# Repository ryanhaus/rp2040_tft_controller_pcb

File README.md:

# rp2040_tft_controller_pcb
 RP2040-based controller board for the [MI0284QT-11 TFT LCD](https://www.adafruit.com/product/1774) (ILI9341 controller chip) designed in KiCad.<br />
 Future plans are to modify this board to have an FPGA controlling the actual LCD, acting as a GPU, allowing the RP2040 (or another microcontroller) to run more complex programs, see my [ili9341_controller repository](https://github.com/ryanhaus/ili9341_controller).

## PCB Screenshots

## Schematics
Schematics for this PCB can be found in the top directory.<br/>
PDF printouts can be found in the [pdfs](https://github.com/ryanhaus/rp2040_tft_controller_pcb/tree/99923349eaa0201b7b87c9602e28e256294b100d/pdfs) folder.

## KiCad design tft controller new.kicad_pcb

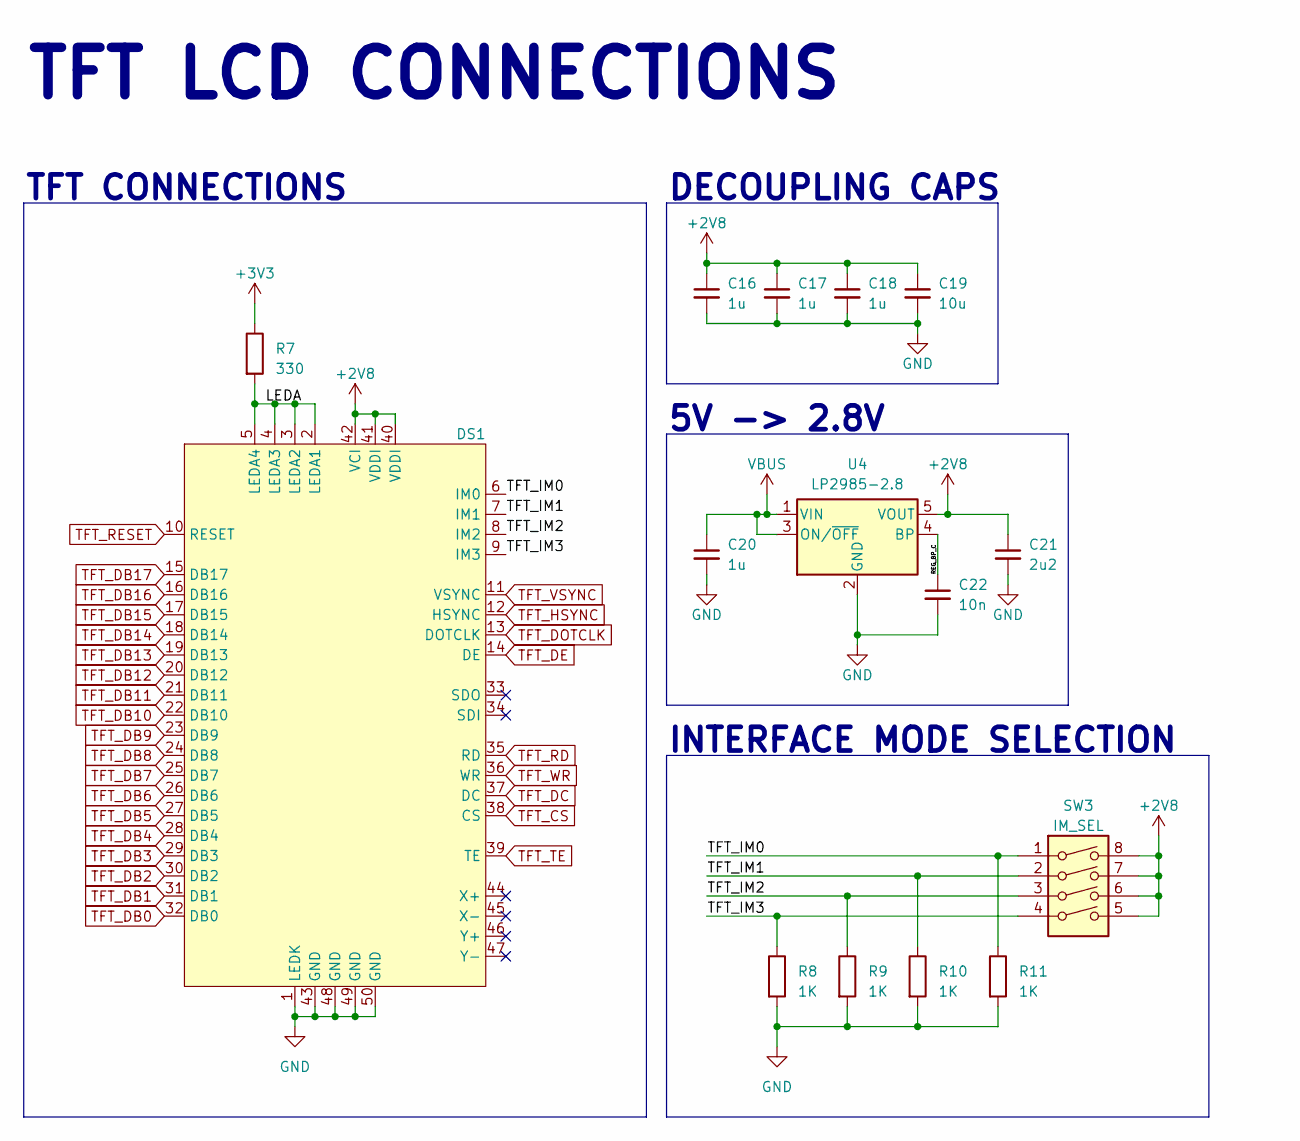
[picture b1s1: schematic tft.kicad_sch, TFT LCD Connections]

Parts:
C16, C17, C18, C20: 1u; C_0603_1608Metric_Pad1.08x0.95mm_HandSolder
C19: 10u; C_0603_1608Metric_Pad1.08x0.95mm_HandSolder
C21: 2u2; C_0603_1608Metric_Pad1.08x0.95mm_HandSolder
C22: 10n; C_0603_1608Metric_Pad1.08x0.95mm_HandSolder
DS1: Molex_54132-5033_1x50-1MP_P0.5mm_Horizontal
R7: 330; R_0603_1608Metric_Pad0.98x0.95mm_HandSolder
R8, R9, R10, R11: 1K; R_0603_1608Metric_Pad0.98x0.95mm_HandSolder
SW3: IM_SEL; SW_DIP_SPSTx04_Slide_9.78x12.34mm_W7.62mm_P2.54mm
U4: LP2985-2.8; SOT-23-5

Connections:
+2V8: C16.1, C17.1, C18.1, C19.1, C21.1, DS1.40 (VDDI), DS1.41 (VDDI), DS1.42 (VCI), SW3.5, SW3.6, SW3.7, SW3.8, U4.5 (VOUT)
+3V3: R7.1; also elsewhere on the board
/TFT LCD Connections/LEDA: DS1.2 (LEDA1), DS1.3 (LEDA2), DS1.4 (LEDA3), DS1.5 (LEDA4), R7.2
/TFT LCD Connections/REG_BP_C: C22.1, U4.4 (BP)
/TFT LCD Connections/TFT_IM0: DS1.6 (IM0), R11.1, SW3.1
/TFT LCD Connections/TFT_IM1: DS1.7 (IM1), R10.1, SW3.2
/TFT LCD Connections/TFT_IM2: DS1.8 (IM2), R9.1, SW3.3
/TFT LCD Connections/TFT_IM3: DS1.9 (IM3), R8.1, SW3.4
GND: C16.2, C17.2, C18.2, C19.2, C20.2, C21.2, C22.2, DS1.1 (LEDK), DS1.43 (GND), DS1.48 (GND), DS1.49 (GND), DS1.50 (GND), R8.2, R9.2, R10.2, R11.2, U4.2 (GND); also elsewhere on the board
TFT_CS: DS1.38 (CS); also elsewhere on the board
TFT_DB0: DS1.32 (DB0); also elsewhere on the board
TFT_DB1: DS1.31 (DB1); also elsewhere on the board
TFT_DB2: DS1.30 (DB2); also elsewhere on the board
TFT_DB3: DS1.29 (DB3); also elsewhere on the board
TFT_DB4: DS1.28 (DB4); also elsewhere on the board
TFT_DB5: DS1.27 (DB5); also elsewhere on the board
TFT_DB6: DS1.26 (DB6); also elsewhere on the board
TFT_DB7: DS1.25 (DB7); also elsewhere on the board
TFT_DB8: DS1.24 (DB8); also elsewhere on the board
TFT_DB9: DS1.23 (DB9); also elsewhere on the board
TFT_DB10: DS1.22 (DB10); also elsewhere on the board
TFT_DB11: DS1.21 (DB11); also elsewhere on the board
TFT_DB12: DS1.20 (DB12); also elsewhere on the board
TFT_DB13: DS1.19 (DB13); also elsewhere on the board
TFT_DB14: DS1.18 (DB14); also elsewhere on the board
TFT_DB15: DS1.17 (DB15); also elsewhere on the board
TFT_DB16: DS1.16 (DB16); also elsewhere on the board
TFT_DB17: DS1.15 (DB17); also elsewhere on the board
TFT_DC: DS1.37 (DC); also elsewhere on the board
TFT_DE: DS1.14 (DE); also elsewhere on the board
TFT_DOTCLK: DS1.13 (DOTCLK); also elsewhere on the board
TFT_HSYNC: DS1.12 (HSYNC); also elsewhere on the board
TFT_RD: DS1.35 (RD); also elsewhere on the board
TFT_RESET: DS1.10 (RESET); also elsewhere on the board
TFT_TE: DS1.39 (TE); also elsewhere on the board
TFT_VSYNC: DS1.11 (VSYNC); also elsewhere on the board
TFT_WR: DS1.36 (WR); also elsewhere on the board
VBUS: C20.1, U4.1 (VIN), U4.3 (ON/~OFF); also elsewhere on the board

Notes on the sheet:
TFT CONNECTIONS
DECOUPLING CAPS
INTERFACE MODE SELECTION
TFT LCD CONNECTIONS
5V -> 2.8V

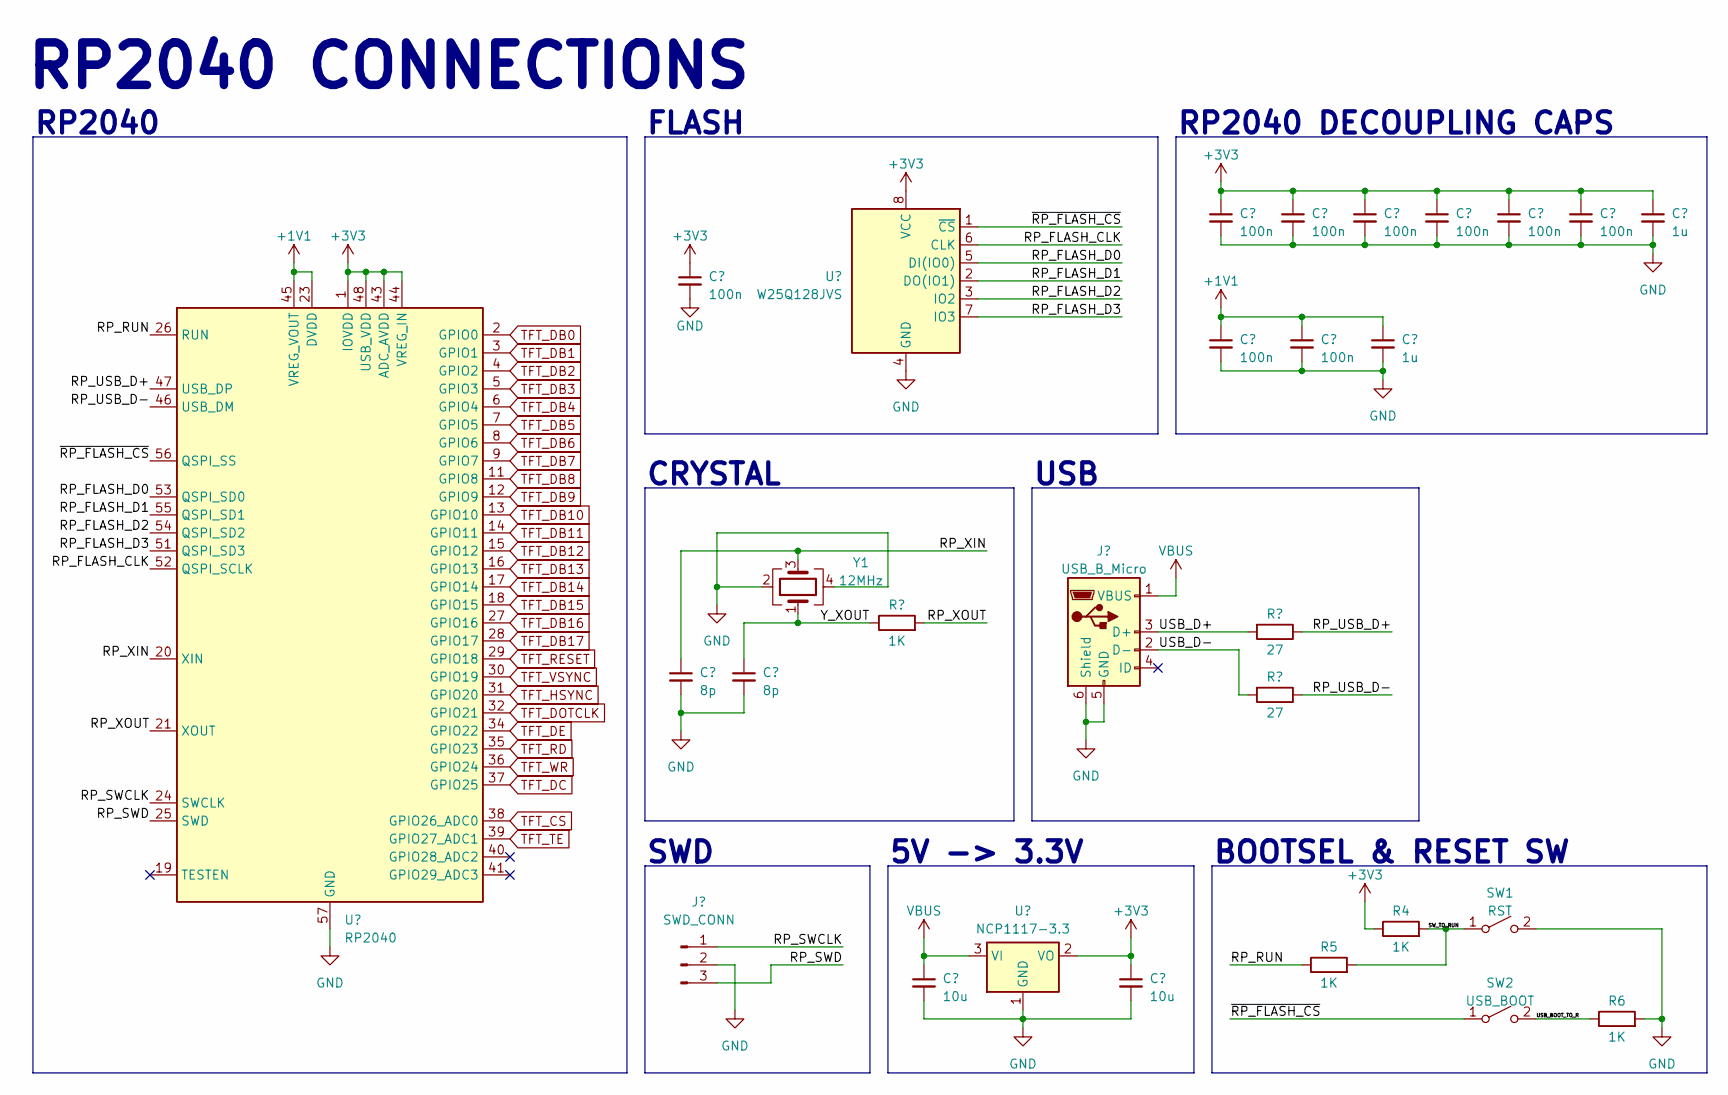
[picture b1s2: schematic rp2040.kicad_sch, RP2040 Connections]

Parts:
C1, C2, C3, C4, C5, C6, C8, C9, C10: 100n; C_0603_1608Metric_Pad1.08x0.95mm_HandSolder
C7, C11: 1u; C_0603_1608Metric_Pad1.08x0.95mm_HandSolder
C12, C13: 8p; C_0603_1608Metric_Pad1.08x0.95mm_HandSolder
C14, C15: 10u; C_0603_1608Metric_Pad1.08x0.95mm_HandSolder
J1: USB_B_Micro; USB_Micro-B_Molex-105017-0001
J3: SWD_CONN; PinSocket_1x03_P2.54mm_Vertical
R1, R4, R5, R6: 1K; R_0603_1608Metric_Pad0.98x0.95mm_HandSolder
R2, R3: 27; R_0603_1608Metric_Pad0.98x0.95mm_HandSolder
SW1: RST; SW_SPST_TL3305A
SW2: USB_BOOT; SW_SPST_TL3305A
U1: W25Q128JVS; WSON-8-1EP_6x5mm_P1.27mm_EP3.4x4mm
U2: RP2040; QFN-56-1EP_7x7mm_P0.4mm_EP3.2x3.2mm
U3: NCP1117-3.3; SOT-223-3_TabPin2
Y1: 12MHz; Crystal_SMD_2520-4Pin_2.5x2.0mm

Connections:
+1V1: C9.1, C10.1, C11.1, U2.23 (DVDD), U2.45 (VREG_VOUT), U2.50 (DVDD)
+3V3: C1.1, C2.1, C3.1, C4.1, C5.1, C6.1, C7.1, C8.1, C15.1, R4.1, U1.8 (VCC), U2.1 (IOVDD), U2.10 (IOVDD), U2.22 (IOVDD), U2.33 (IOVDD), U2.42 (IOVDD), U2.43 (ADC_AVDD), U2.44 (VREG_IN), U2.48 (USB_VDD), U2.49 (IOVDD), U3.2 (VO); also elsewhere on the board
/RP2040 Connections/RP_FLASH_CLK: U1.6 (CLK), U2.52 (QSPI_SCLK)
/RP2040 Connections/RP_FLASH_D0: U1.5 (DI(IO0)), U2.53 (QSPI_SD0)
/RP2040 Connections/RP_FLASH_D1: U1.2 (DO(IO1)), U2.55 (QSPI_SD1)
/RP2040 Connections/RP_FLASH_D2: U1.3 (IO2), U2.54 (QSPI_SD2)
/RP2040 Connections/RP_FLASH_D3: U1.7 (IO3), U2.51 (QSPI_SD3)
/RP2040 Connections/RP_RUN: R5.1, U2.26 (RUN)
/RP2040 Connections/RP_SWCLK: J3.1, U2.24 (SWCLK)
/RP2040 Connections/RP_SWD: J3.3, U2.25 (SWD)
/RP2040 Connections/RP_USB_D+: R2.1, U2.47 (USB_DP)
/RP2040 Connections/RP_USB_D-: R3.1, U2.46 (USB_DM)
/RP2040 Connections/RP_XIN: C12.1, U2.20 (XIN), Y1.3
/RP2040 Connections/RP_XOUT: R1.2, U2.21 (XOUT)
/RP2040 Connections/SW_TO_RUN: R4.2, R5.2, SW1.1 (A)
/RP2040 Connections/USB_BOOT_TO_R: R6.1, SW2.2 (B)
/RP2040 Connections/USB_D+: J1.3 (D+), R2.2
/RP2040 Connections/USB_D-: J1.2 (D-), R3.2
/RP2040 Connections/Y_XOUT: C13.1, R1.1, Y1.1
/RP2040 Connections/~RP_FLASH_CS: SW2.1 (A), U1.1 (~CS), U2.56 (QSPI_SS)
GND: C1.2, C2.2, C3.2, C4.2, C5.2, C6.2, C7.2, C8.2, C9.2, C10.2, C11.2, C12.2, C13.2, C14.2, C15.2, J1.5 (GND), J1.6 (Shield), J3.2, R6.2, SW1.2 (B), U1.4 (GND), U1.9, U2.57 (GND), U3.1 (GND), Y1.2, Y1.4; also elsewhere on the board
TFT_CS: U2.38 (GPIO26_ADC0); also elsewhere on the board
TFT_DB0: U2.2 (GPIO0); also elsewhere on the board
TFT_DB1: U2.3 (GPIO1); also elsewhere on the board
TFT_DB2: U2.4 (GPIO2); also elsewhere on the board
TFT_DB3: U2.5 (GPIO3); also elsewhere on the board
TFT_DB4: U2.6 (GPIO4); also elsewhere on the board
TFT_DB5: U2.7 (GPIO5); also elsewhere on the board
TFT_DB6: U2.8 (GPIO6); also elsewhere on the board
TFT_DB7: U2.9 (GPIO7); also elsewhere on the board
TFT_DB8: U2.11 (GPIO8); also elsewhere on the board
TFT_DB9: U2.12 (GPIO9); also elsewhere on the board
TFT_DB10: U2.13 (GPIO10); also elsewhere on the board
TFT_DB11: U2.14 (GPIO11); also elsewhere on the board
TFT_DB12: U2.15 (GPIO12); also elsewhere on the board
TFT_DB13: U2.16 (GPIO13); also elsewhere on the board
TFT_DB14: U2.17 (GPIO14); also elsewhere on the board
TFT_DB15: U2.18 (GPIO15); also elsewhere on the board
TFT_DB16: U2.27 (GPIO16); also elsewhere on the board
TFT_DB17: U2.28 (GPIO17); also elsewhere on the board
TFT_DC: U2.37 (GPIO25); also elsewhere on the board
TFT_DE: U2.34 (GPIO22); also elsewhere on the board
TFT_DOTCLK: U2.32 (GPIO21); also elsewhere on the board
TFT_HSYNC: U2.31 (GPIO20); also elsewhere on the board
TFT_RD: U2.35 (GPIO23); also elsewhere on the board
TFT_RESET: U2.29 (GPIO18); also elsewhere on the board
TFT_TE: U2.39 (GPIO27_ADC1); also elsewhere on the board
TFT_VSYNC: U2.30 (GPIO19); also elsewhere on the board
TFT_WR: U2.36 (GPIO24); also elsewhere on the board
VBUS: C14.1, J1.1 (VBUS), U3.3 (VI); also elsewhere on the board

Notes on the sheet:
CRYSTAL
RP2040 DECOUPLING CAPS
USB
RP2040 CONNECTIONS
BOOTSEL & RESET SW
SWD
5V -> 3.3V
RP2040
FLASH

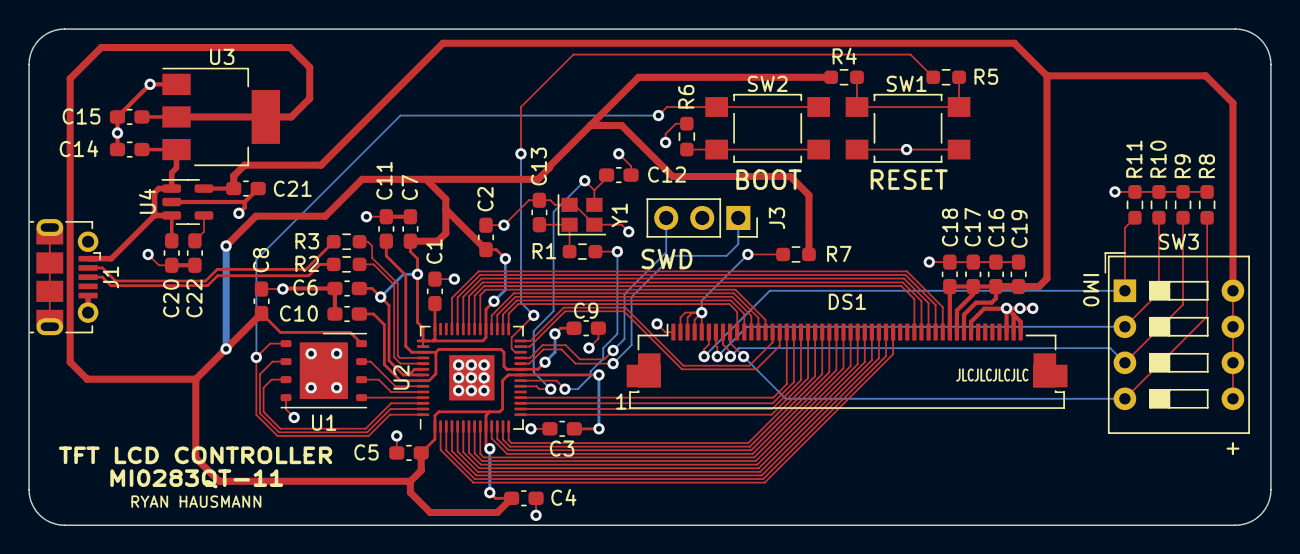
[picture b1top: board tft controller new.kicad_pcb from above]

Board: 4 copper layers, 87.6 x 35.0 mm, 44 parts (0 on the bottom side), 57 nets.

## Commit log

2023-10-31 add screenshots of pcb render
